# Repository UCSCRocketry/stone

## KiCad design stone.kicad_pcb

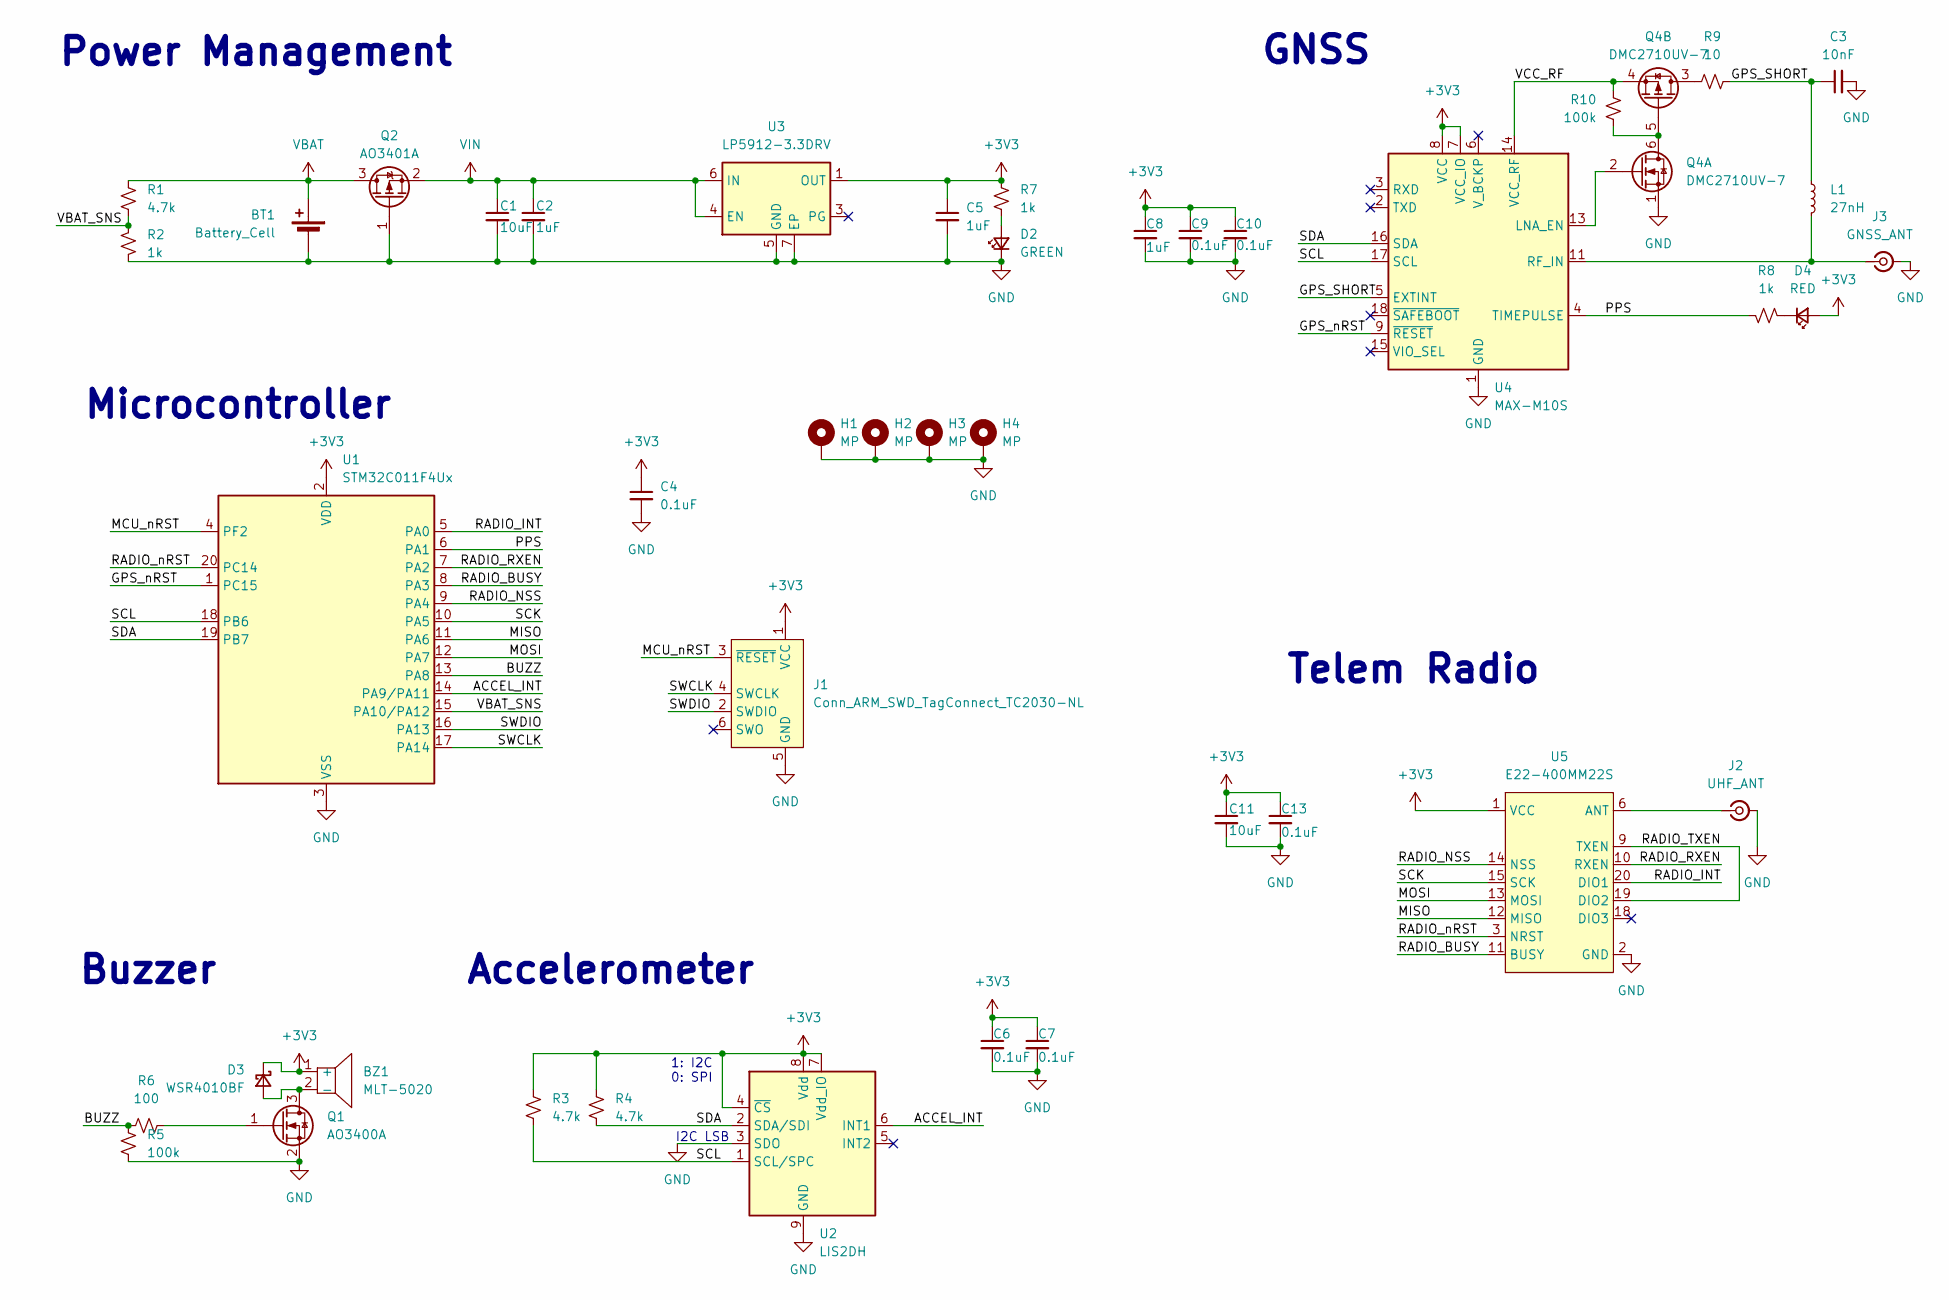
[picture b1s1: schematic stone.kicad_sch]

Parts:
BT1: Battery_Cell; JST_PH_B2B-PH-K_1x02_P2.00mm_Vertical; MPN B2B-PH-K-S(LF)(SN); LCSC Part # C131337
BZ1: MLT-5020; MPN MLT-5020; LCSC Part C94598
C1, C11: 10uF; C_0603_1608Metric; Tolerance 10%; Voltage Rating 10V; MPN CL10A106KP8NNNC; LCSC Part # C19702
C2, C5, C8: 1uF; C_0402_1005Metric; MPN CL05A105KA5NQNC; LCSC Part # C52923
C3: 10nF; C_0402_1005Metric; Tolerance 10%; Voltage Rating 50V; MPN CL05B103KB5NNNC; JLCPCB Part Class Basic
C4, C6, C7, C9, C10, C13: 0.1uF; C_0402_1005Metric; MPN CL05B104KO5NNNC; LCSC Part # C1525
D2: GREEN; LED_0402_1005Metric; MPN F.0402.00001/P2-0402G1TS2-045T-001; LCSC Part # C7496801
D3: WSR4010BF; WSR4010BF_DFN1006-2L; MPN WSR4010BF; LCSC Part # C3039428
D4: RED; LED_0402_1005Metric; MPN SZYY0402R; LCSC Part # C434445
H1, H2, H3, H4: MP; MountingHole_2.2mm_M2_Pad
J1: Conn_ARM_SWD_TagConnect_TC2030-NL; Tag-Connect_TC2030-IDC-NL_2x03_P1.27mm_Vertical
J2: UHF_ANT; SMA_Kinghelm_KH-SMA-KE8-G_EdgeMount_1.6mm; MPN KH-SMA-KE8-G; LCSC Part # C530661
J3: GNSS_ANT; U.FL_Molex_MCRF_73412-0110_Vertical; MPN U.FL-R-SMT-1(80); LCSC Part # C88374
L1: 27nH; L_0402_1005Metric; Current Rating 300mA; Tolerance 5%; MPN LQG15HN27NJ02D; JLCPCB Part Class Extended
Q1: AO3400A; SOT-23; MPN AO3400A; LCSC Part # C20917
Q2: AO3401A; SOT-23
Q4: DMC2710UV-7; DMC2710UV_SOT-563; MPN DMC2710UV-7; LCSC Part # C5245238
R1, R3, R4: 4.7k; R_0402_1005Metric; MPN 0402WGF4701TCE; JLCPCB Part Class Basic
R2, R7, R8: 1k; R_0402_1005Metric; MPN 0402WGF1001TCE; LCSC Part # C11702
R5, R10: 100k; R_0402_1005Metric; MPN 0402WGF1003TCE; JLCPCB Part Class Basic
R6: 100; R_0402_1005Metric; MPN 0402WGF1000TCE; JLCPCB Part Class Basic
R9: 10; R_0402_1005Metric; Power Rating 0.25W; Tolerance 1%; MPN ERJPA2F10R0X; JLCPCB Part Class Extended
U1: STM32C011F4Ux; ST_UFQFPN-20_3x3mm_P0.5mm; MPN STM32C011F4U6TR; LCSC Part # C5456188
U2: LIS2DH; LGA-14_2x2mm_P0.35mm_LayoutBorder3x4y; MPN LIS2DHTR; LCSC Part # C155670
U3: LP5912-3.3DRV; WSON-6-1EP_2x2mm_P0.65mm_EP1x1.6mm; MPN LP5912-3.3DRVT; LCSC Part # C134121
U4: MAX-M10S; ublox_MAX; MPN MAX-M10S-00B; LCSC Part # C4153167
U5: E22-400MM22S; E22-20_10x10; MPN E22-400MM22S; LCSC Part # C5333984

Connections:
+3V3: BZ1.1 (+), C4.1, C5.1, C6.1, C7.1, C8.1, C9.1, C10.1, C11.1, C13.1, D3.1 (K), D4.2 (A), J1.1 (VCC), R3.1, R4.1, R7.1, U1.2 (VDD), U2.4 (~CS), U2.7 (Vdd_IO), U2.8 (Vdd), U3.1 (OUT), U4.7 (VCC_IO), U4.8 (VCC), U5.1 (VCC)
/ACCEL_INT: U1.14 (PA9/PA11), U2.6 (INT1)
/BUZZ: R5.1, R6.1, U1.13 (PA8)
/GPS_SHORT: C3.1, L1.1, R9.2, U4.5 (EXTINT)
/GPS_nRST: U1.1 (PC15), U4.9 (~RESET)
/MCU_nRST: J1.3 (~RESET), U1.4 (PF2)
/MISO: U1.11 (PA6), U5.12 (MISO)
/MOSI: U1.12 (PA7), U5.13 (MOSI)
/PPS: R8.2, U1.6 (PA1), U4.4 (TIMEPULSE)
/RADIO_BUSY: U1.8 (PA3), U5.11 (BUSY)
/RADIO_INT: U1.5 (PA0), U5.20 (DIO1)
/RADIO_NSS: U1.9 (PA4), U5.14 (NSS)
/RADIO_RXEN: U1.7 (PA2), U5.10 (RXEN)
/RADIO_TXEN: U5.9 (TXEN), U5.19 (DIO2)
/RADIO_nRST: U1.20 (PC14), U5.3 (NRST)
/SCK: U1.10 (PA5), U5.15 (SCK)
/SCL: R3.2, U1.18 (PB6), U2.1 (SCL/SPC), U4.17 (SCL)
/SDA: R4.2, U1.19 (PB7), U2.2 (SDA/SDI), U4.16 (SDA)
/SWCLK: J1.4 (SWCLK), U1.17 (PA14)
/SWDIO: J1.2 (SWDIO), U1.16 (PA13)
/VBAT_SNS: R1.2, R2.1, U1.15 (PA10/PA12)
/VCC_RF: Q4.4 (S), R10.1, U4.14 (VCC_RF)
GND: BT1.2 (-), C1.2, C2.2, C3.2, C4.2, C5.2, C6.2, C7.2, C8.2, C9.2, C10.2, C11.2, C13.2, D2.1 (K), H1.1 (1_1), H2.1 (1_1), H3.1 (1_1), H4.1 (1_1), J1.5 (GND), J2.2 (Ext), J3.2 (Ext), Q1.2 (S), Q2.1 (G), Q4.1 (S), R2.2, R5.2, U1.3 (VSS), U2.3 (SDO), U2.9 (GND), U2.10 (GND), U2.11 (GND), U2.12 (GND), U2.13 (GND), U2.14 (GND), U3.5 (GND), U3.7 (EP), U4.1 (GND), U4.10 (GND), U4.12 (GND), U5.2 (GND), U5.7 (GND), U5.16 (GND)
unnamed: BZ1.2 (-), D3.2 (A), Q1.3 (D)
unnamed: D2.2 (A), R7.2
unnamed: D4.1 (K), R8.1
unnamed: J2.1 (In), U5.6 (ANT)
unnamed: J3.1 (In), L1.2, U4.11 (RF_IN)
unnamed: Q1.1 (G), R6.2
unnamed: Q4.5 (G), Q4.6 (D), R10.2
unnamed: Q4.2 (G), U4.13 (LNA_EN)
unnamed: Q4.3 (D), R9.1
VBAT: BT1.1 (+), Q2.3 (D), R1.1
VIN: C1.1, C2.1, Q2.2 (S), U3.4 (EN), U3.6 (IN)

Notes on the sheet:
Microcontroller
Buzzer
1: I2C 0: SPI
Telem Radio
I2C LSB
GNSS
Power Management
Accelerometer

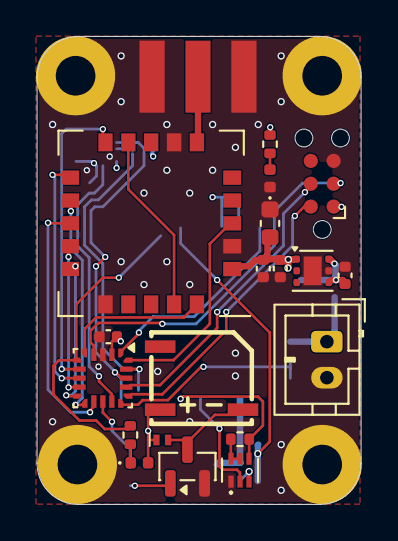
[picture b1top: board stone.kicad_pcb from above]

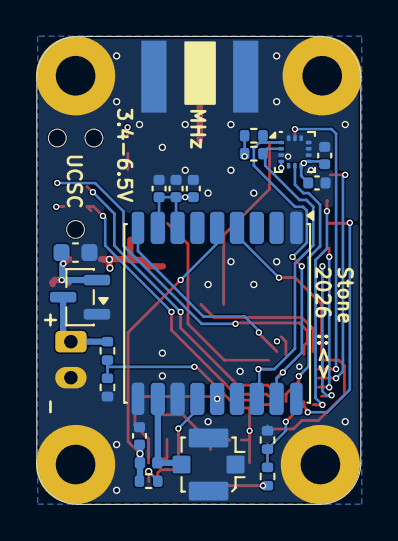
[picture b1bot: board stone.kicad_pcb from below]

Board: 4 copper layers, 18.0 x 26.0 mm, 43 parts (19 on the bottom side), 34 nets.

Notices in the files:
parts and their libraries:
Diodes DS41423 Rev.4-2 June 2021 pp.1-3,8; symbol graphics adapted from KiCad Transistor_FET (CC-BY-SA 4.0 with symbol exception). Unit A NMOS, unit B PMOS. Internal gate protection is specified by the datasheet, not represented in generic MOSFET graphics.
